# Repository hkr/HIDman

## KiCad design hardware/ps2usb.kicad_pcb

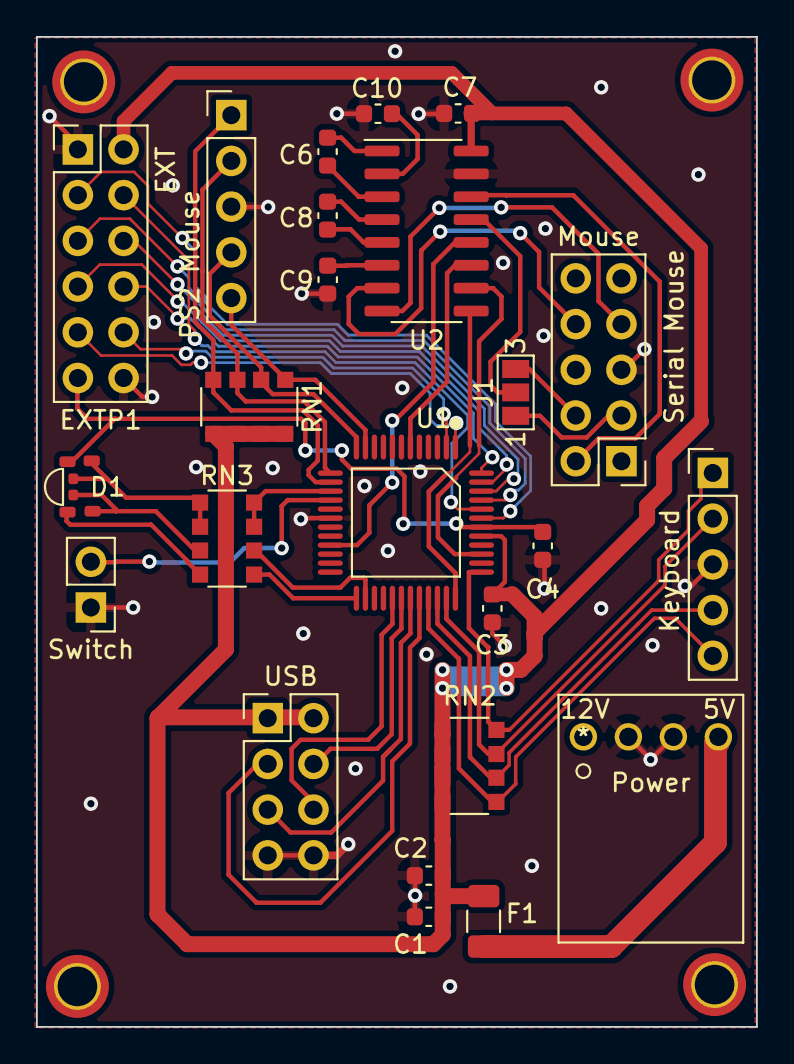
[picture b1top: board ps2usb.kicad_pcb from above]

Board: 2 copper layers, 40.0 x 55.0 mm, 24 parts (0 on the bottom side), 45 nets.

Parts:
C1, C2, C4: 3.3u; C_0603_1608Metric
C3: 100n; C_0603_1608Metric
C6, C7, C8, C9, C10: 1u; C_0603_1608Metric
D1: B3173BGR-20C0001Q3U1930
EXT: EXTP1; PinHeader_2x06_P2.54mm_Vertical
F1: 500mA; Fuse_1206_3216Metric
J1: J1; SolderJumper-3_P1.3mm_Open_Pad1.0x1.5mm_NumberLabels
Keyboard: Keyboard; PinHeader_1x05_P2.54mm_Vertical
PS2 Mouse: PS2 Mouse; PinHeader_1x05_P2.54mm_Vertical
Power: CONN_171826-4_TYCO_TYC; 171826-4
RN1, RN2, RN3: R_Pack04; R_Array_Convex_4x1206
Serial Mouse: Mouse; PinHeader_2x05_P2.54mm_Vertical
Switch: PinHeader_1x02_P2.54mm_Vertical
U1: CH559L-less; QFP-12x12_14x14_Pitch0.5mm
U2: MAX232; SOIC-16_3.9x9.9mm_P1.27mm
USB: USB; PinHeader_2x04_P2.54mm_Vertical

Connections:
+3.3V: C4.2, D1.1, EXT.11, U1.42 (VDD33)
+5V: C1.2, C2.2, C3.2, C7.2, EXT.2, F1.1, RN1.5 (R4.2), RN1.6 (R3.2), RN1.7 (R2.2), RN1.8 (R1.2), RN2.5 (R4.2), RN2.6 (R3.2), RN2.7 (R2.2), RN2.8 (R1.2), U1.41 (VIN5), U2.16 (VCC), USB.1, USB.2
/CTS_232: Serial Mouse.8, U2.7 (T2OUT)
/CTS_MCU: U1.36 (P0.4/AD4/UCTS), U2.9 (R2OUT)
/DIN1-1: PS2 Mouse.1, RN1.4 (R4.1), U1.14 (P4.3/PWM1_/A3)
/DIN1-2: PS2 Mouse.4, RN1.2 (R2.1), U1.12 (P3.6/WR)
/DIN1-6: PS2 Mouse.2, RN1.3 (R3.1), U1.13 (P3.7/RD)
/DIN1-8: PS2 Mouse.5, RN1.1 (R1.1), U1.11 (P3.5/DA6/T1)
/DIN2-1: Keyboard.1, RN2.4 (R4.1), U1.37 (P0.3/AD3/TXD_)
/DIN2-2: Keyboard.4, RN2.2 (R2.1), U1.34 (P0.6/AD6/URI)
/DIN2-6: Keyboard.2, RN2.3 (R3.1), U1.35 (P0.5/AD5/UDSR)
/DIN2-8: Keyboard.5, RN2.1 (R1.1), U1.33 (P0.7/AD7/UDCD)
/DTR_232: J1.2, J1.3, Serial Mouse.4, U2.13 (R1IN)
/DTR_MCU: U1.21 (P2.0/A8), U2.12 (R1OUT)
/EXT1: EXT.3, U1.43
/EXT2: EXT.4, U1.44
/EXT3: EXT.5, U1.45
/EXT4: EXT.6, U1.46
/EXT5: EXT.7, U1.47
/EXT6: EXT.8, U1.48
/EXT7: EXT.9, U1.1
/EXT8: EXT.10, U1.2
/RTS_232: Serial Mouse.7, U2.8 (R2IN)
/RTS_MCU: U1.39 (P0.1/AD1/URTS), U2.10 (T2IN)
/RXD_232: Serial Mouse.2, U2.14 (T1OUT)
/TXD_MCU: U1.6 (P4.4/LED3/TNOW_/TXD1_/A4), U2.11 (T1IN)
GND: C1.1, C2.1, C3.1, C4.1, C7.1, C9.2, C10.1, EXT.1, EXT.12, Keyboard.3, PS2 Mouse.3, Power.2, Power.3, Serial Mouse.5, Switch.1, U1.18 (GND), U2.15 (GND), USB.7, USB.8
unnamed: C6.1, U2.3 (C1-)
unnamed: C6.2, U2.1 (C1+)
unnamed: C8.1, U2.5 (C2-)
unnamed: C8.2, U2.4 (C2+)
unnamed: C9.1, U2.6 (VS-)
unnamed: C10.2, U2.2 (VS+)
unnamed: D1.2 (B), RN3.1 (R1.1), RN3.2 (R2.1)
unnamed: D1.3 (G), RN3.3 (R3.1)
unnamed: D1.4 (R), RN3.4 (R4.1)
unnamed: F1.2, Power.4
unnamed: U1.30 (P5.4/HM/ALE/XB), USB.4
unnamed: U1.32 (P5.0/DM), USB.3
unnamed: U1.29 (P5.5/HP/!A15/XA), USB.6
unnamed: U1.31 (P5.1/DP), USB.5
unnamed: RN3.5 (R4.2), U1.25 (P2.4/PWM1/A12)
unnamed: RN3.6 (R3.2), U1.26 (P2.5/TNOW/PWM2)
unnamed: RN3.7 (R2.2), RN3.8 (R1.2), U1.15 (P4.2/PWM3_/CAP3_/A2)
unnamed: Switch.2, U1.16 (P4.6/XI/SCS_)

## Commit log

2023-01-29 Internal version, replaced connectors with headers

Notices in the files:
parts and their libraries:
Copyright 2021 Accelerated Designs. All rights reserved.
